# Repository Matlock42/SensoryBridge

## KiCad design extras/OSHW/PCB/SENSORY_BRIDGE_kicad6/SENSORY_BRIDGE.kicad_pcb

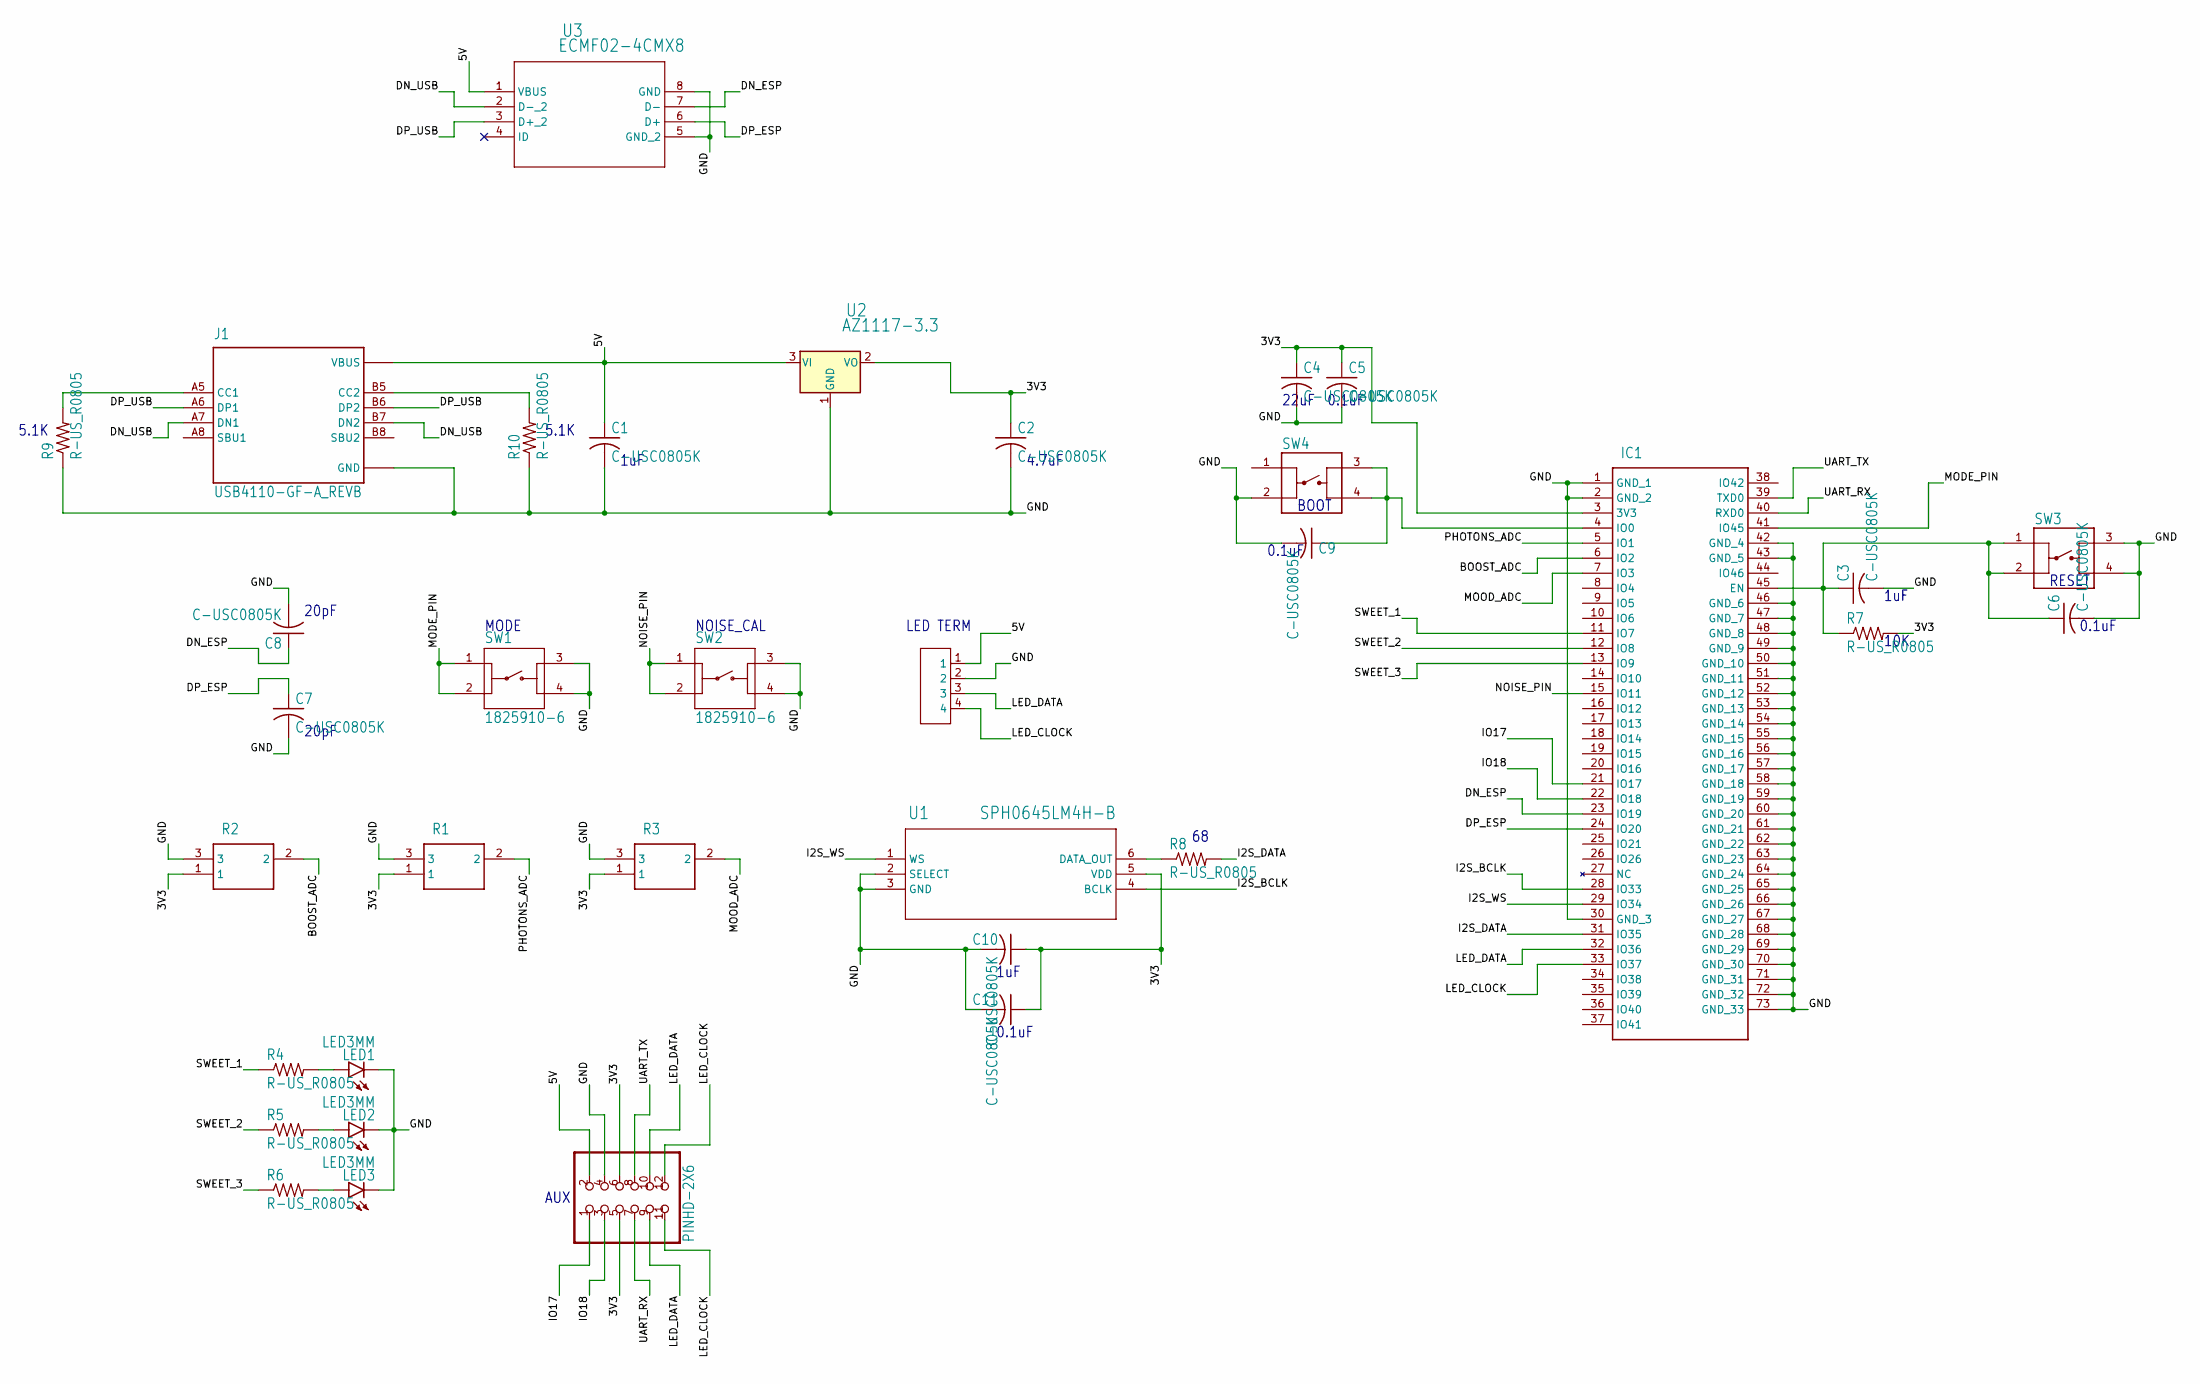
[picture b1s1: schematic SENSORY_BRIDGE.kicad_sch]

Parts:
C1, C2, C3, C4, C5, C6, C7, C8, C9, C10, C11: C-USC0805K; C0805K
IC1: ESP32-S2-MINI-1-N4R2; ESP32S2MINI1N4R2
J1: USB4110-GF-A_REVB; GCT_USB4110-GF-A_REVB
J2: 796949-4; TE_796949-4
JP1: PINHD-2X6; 2X06
LED1, LED2, LED3: LED3MM
R1, R2, R3: 3386P-1-103LF; 3386P_1
R4, R5, R6, R7, R8, R9, R10: R-US_R0805; R0805
SW1, SW2: 1825910-6; SW_1825910-6-4
SW3, SW4: PTS525SM15SMTR2LFS; SW_PTS525SM15SMTR2LFS
U1: SPH0645LM4H-B; SPH0645LM4H-B_KNO
U2: AZ1117-3.3; SOT-223_DIO-M
U3: ECMF02-4CMX8; MICRO_QFN-8L_STM

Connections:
/3V3: C2.1, C4.1, C5.1, C10.1, C11.1, IC1.3 (3V3), JP1.5, JP1.6, R1.1, R2.1, R3.1, R7.2, U1.5 (VDD), U2.2 (VO)
/5V: C1.1, J1.A4/B9 (VBUS), J1.B4/A9 (VBUS), J2.1, JP1.2, U2.3 (VI), U3.1 (VBUS)
/BOOST_ADC: IC1.6 (IO2), R2.2
/DN_ESP: C8.1, IC1.23 (IO19), U3.7 (D-)
/DN_USB: J1.A7 (DN1), J1.B7 (DN2), U3.2 (D-_2)
/DP_ESP: C7.1, IC1.24 (IO20), U3.6 (D+)
/DP_USB: J1.A6 (DP1), J1.B6 (DP2), U3.3 (D+_2)
/GND: C1.2, C2.2, C3.2, C4.2, C5.2, C6.2, C7.2, C8.2, C9.2, C10.2, C11.2, IC1.1 (GND_1), IC1.2 (GND_2), IC1.30 (GND_3), IC1.42 (GND_4), IC1.43 (GND_5), IC1.46 (GND_6), IC1.47 (GND_7), IC1.48 (GND_8), IC1.49 (GND_9), IC1.50 (GND_10), IC1.51 (GND_11), IC1.52 (GND_12), IC1.53 (GND_13), IC1.54 (GND_14), IC1.55 (GND_15), IC1.56 (GND_16), IC1.57 (GND_17), IC1.58 (GND_18), IC1.59 (GND_19), IC1.60 (GND_20), IC1.61 (GND_21), IC1.62 (GND_22), IC1.63 (GND_23), IC1.64 (GND_24), IC1.65 (GND_25), IC1.66 (GND_26), IC1.67 (GND_27), IC1.68 (GND_28), IC1.69 (GND_29), IC1.70 (GND_30), IC1.71 (GND_31), IC1.72 (GND_32), IC1.73 (GND_33), J1.A1/B12 (GND), J1.B1/A12 (GND), J1.S1 (GND), J1.S2 (GND), J1.S3 (GND), J1.S4 (GND), J2.2, JP1.4, LED1.K (C), LED2.K (C), LED3.K (C), R1.3, R2.3, R3.3, R9.1, R10.1, SW1.3, SW1.4, SW2.3, SW2.4, SW3.3, SW3.4, SW4.2, U1.2 (SELECT), U1.3 (GND), U2.1 (GND), U3.5 (GND_2), U3.8 (GND)
/I2S_BCLK: IC1.28 (IO33), U1.4 (BCLK)
/I2S_DATA: IC1.31 (IO35), R8.2
/I2S_WS: IC1.29 (IO34), U1.1 (WS)
/IO17: IC1.21 (IO17), JP1.1
/IO18: IC1.22 (IO18), JP1.3
/LED_CLOCK: IC1.33 (IO37), J2.4, JP1.11, JP1.12
/LED_DATA: IC1.32 (IO36), J2.3, JP1.9, JP1.10
/MODE_PIN: IC1.41 (IO45), SW1.1, SW1.2
/MOOD_ADC: IC1.7 (IO3), R3.2
/NOISE_PIN: IC1.15 (IO11), SW2.1, SW2.2
/PHOTONS_ADC: IC1.5 (IO1), R1.2
/SWEET_1: IC1.11 (IO7), R4.1
/SWEET_2: IC1.12 (IO8), R5.1
/SWEET_3: IC1.13 (IO9), R6.1
/UART_RX: IC1.40 (RXD0), JP1.7
/UART_TX: IC1.39 (TXD0), JP1.8
unnamed: C3.1, C6.1, IC1.45 (EN), R7.1, SW3.1, SW3.2
unnamed: C9.1, IC1.4 (IO0), SW4.3, SW4.4
unnamed: J1.A5 (CC1), R9.2
unnamed: J1.B5 (CC2), R10.2
unnamed: LED1.A, R4.2
unnamed: LED2.A, R5.2
unnamed: LED3.A, R6.2
unnamed: R8.1, U1.6 (DATA_OUT)

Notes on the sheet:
1uF
5.1K
MODE
RESET
BOOT
4.7uF
0.1uF
22uF
AUX
20pF
LED TERM
10K
NOISE_CAL

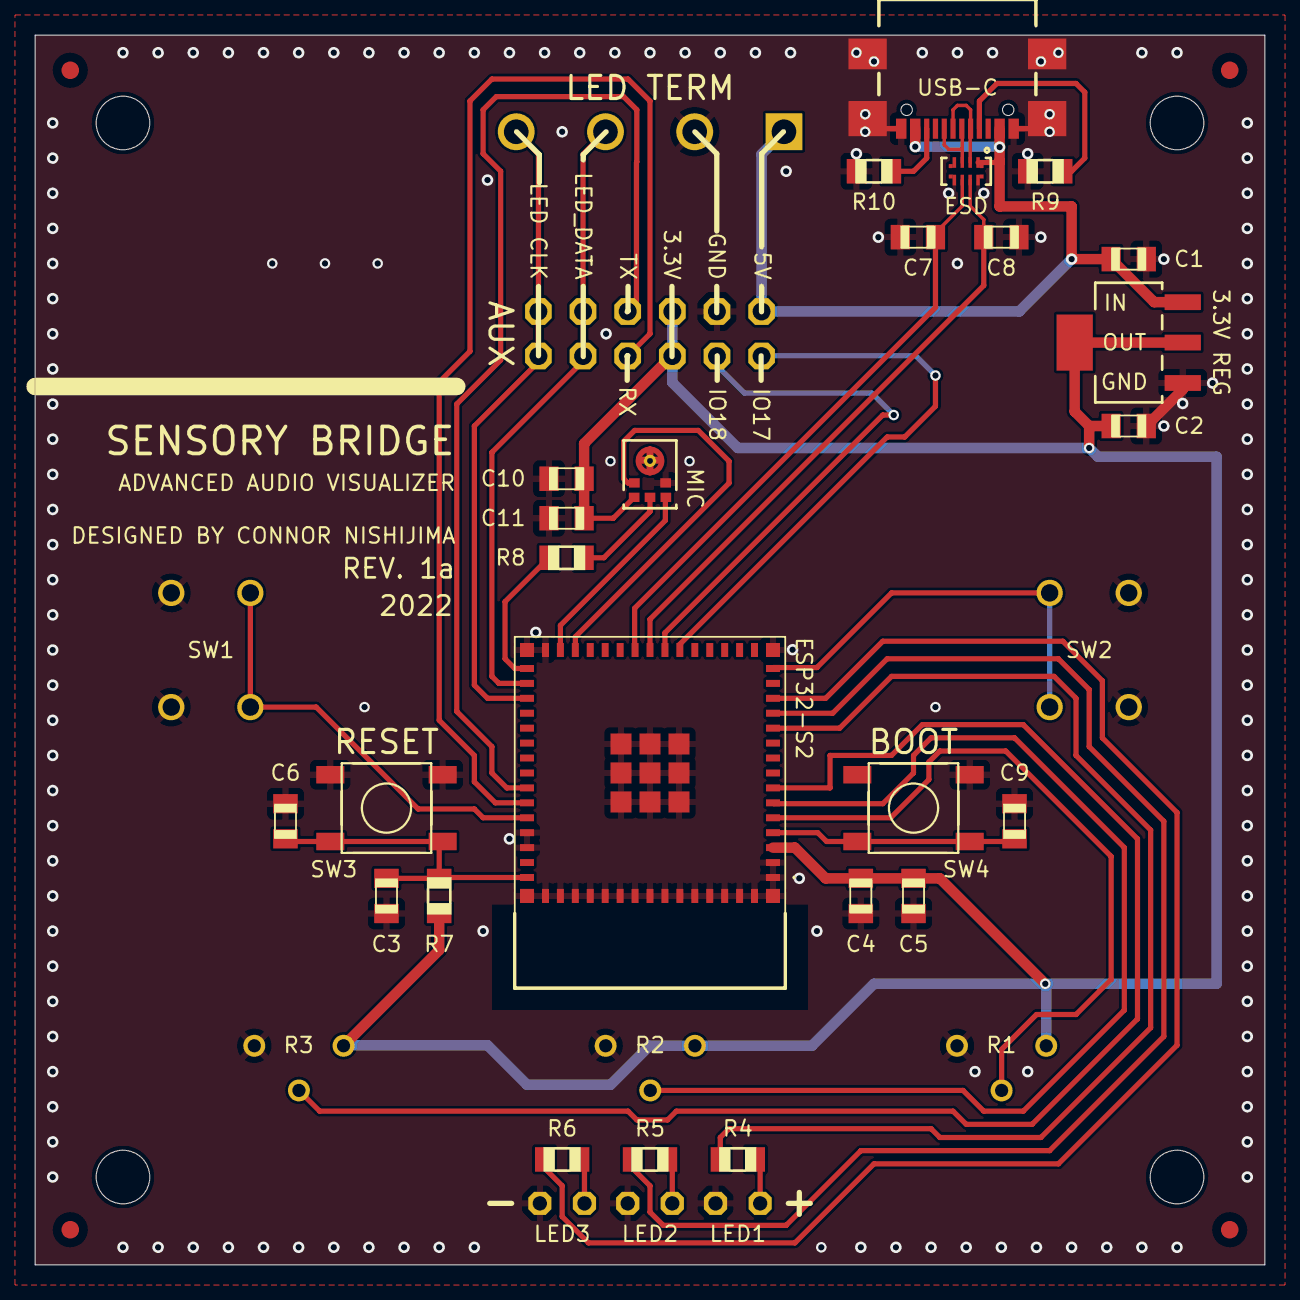
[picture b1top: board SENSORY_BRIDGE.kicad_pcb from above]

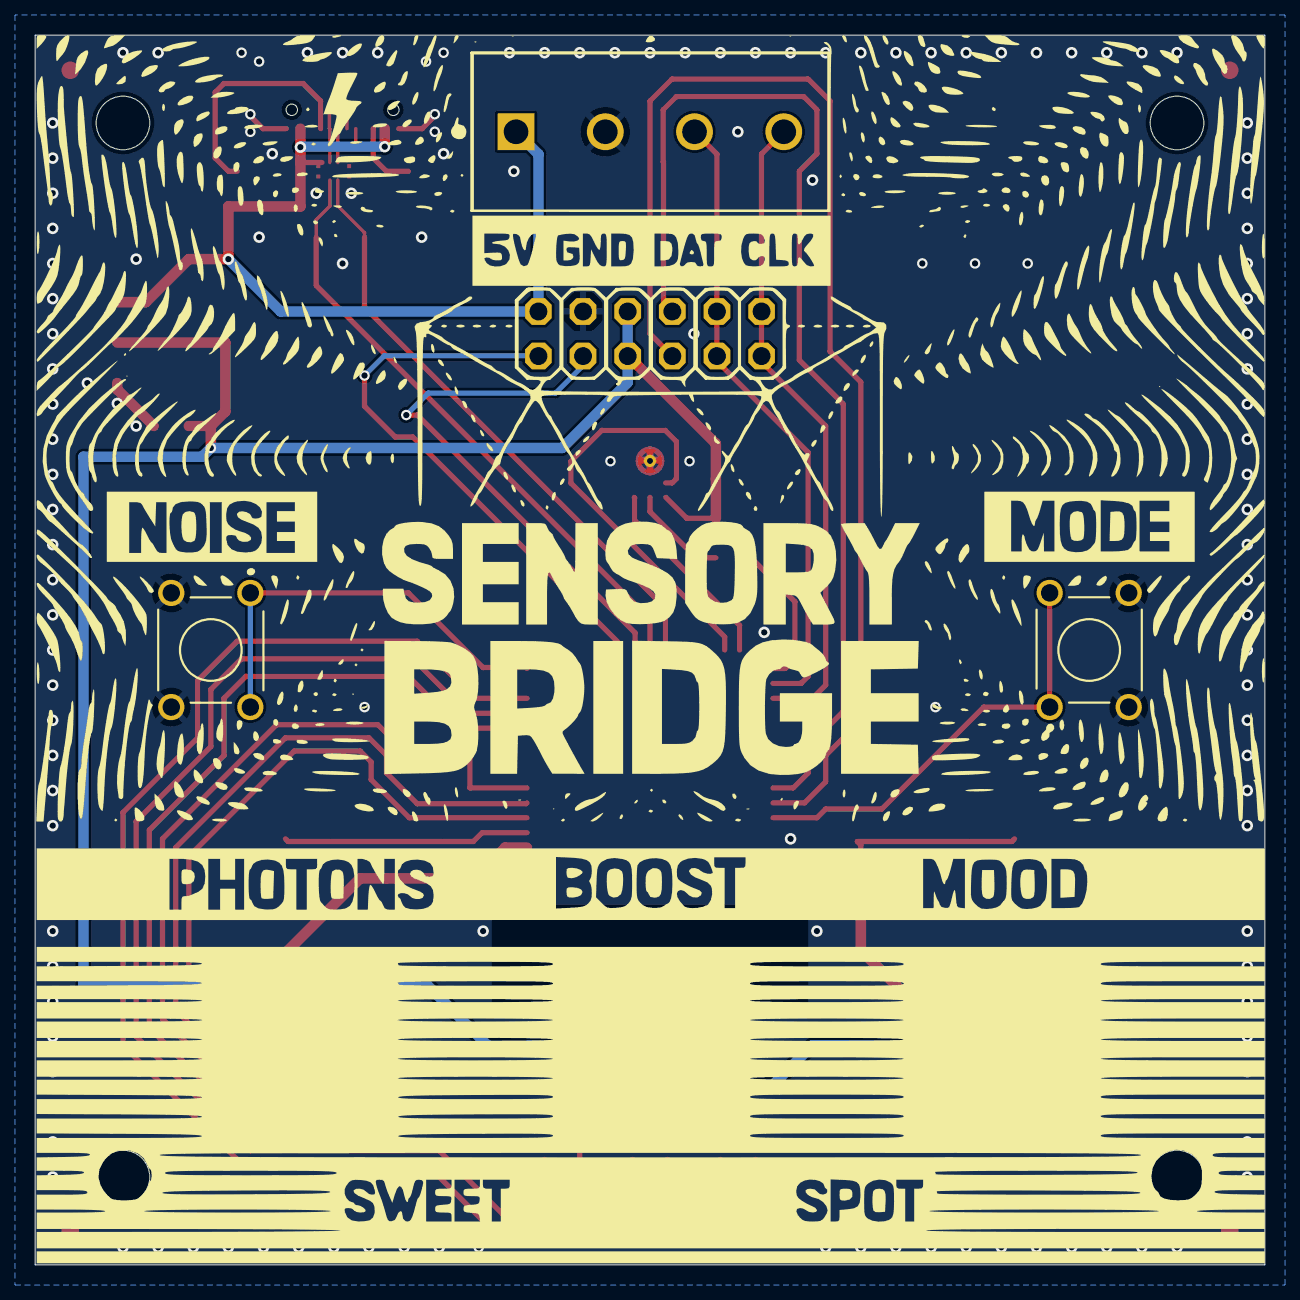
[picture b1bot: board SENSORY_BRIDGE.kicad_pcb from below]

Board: 2 copper layers, 70.0 x 70.0 mm, 43 parts (10 on the bottom side), 32 nets.

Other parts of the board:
@HOLE0, @HOLE1, @HOLE2, @HOLE3: (no value)
U$1, U$2, U$3, U$4: CIRCLE-1MM-2R

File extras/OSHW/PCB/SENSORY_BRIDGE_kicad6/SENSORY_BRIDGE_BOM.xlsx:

Index | Quantity | Part Number | Manufacturer Part Number | Description | Customer Reference | Available | Backorder | Unit Price | Extended Price USD
1 | 1 | 796949-4-ND | 796949-4 | TERM BLK 4P SIDE ENT 5.08MM PCB | J2 | 1 | 0 | 2.93000 | 2.93
2 | 1 | 1965-ESP32-S2-MINI-1-N4R2CT-ND | ESP32-S2-MINI-1-N4R2 | SMD MOD ESP32-S2FN4R2 PCB ANT | IC1 | 1 | 0 | 2.32000 | 2.32
3 | 1 | 497-13420-1-ND | ECMF02-4CMX8 | CMC 2LN SMD ESD | U3 | 1 | 0 | 0.87000 | 0.87
4 | 1 | AP7361-33E-13DICT-ND | AP7361-33E-13 | IC REG LINEAR 3.3V 1A SOT223 | U2 | 0 | 1 | 0.54000 | 0.54
5 | 2 | CKN9104CT-ND | PTS525SM15SMTR2 LFS | SWITCH TACTILE SPST-NO 0.02A 15V | SW3 | 2 | 0 | 0.65000 | 1.30
6 | 1 | 423-1405-1-ND | SPH0645LM4H-B | CRAWFORD MIC DGT I2S BOTTOM PORT | U1 | 1 | 0 | 3.18000 | 3.18
7 | 1 | 2073-USB4110-GF-A-1-ND | USB4110-GF-A | CONN RCP USB2.0 TYP C 24P SMD RA | J1 | 1 | 0 | 1.35000 | 1.35
8 | 3 | 3386P-103TLF-ND | 3386P-1-103TLF | TRIMMER 10K OHM 0.5W PC PIN TOP | R1, R2, R3 | 3 | 0 | 2.50000 | 7.50
9 | 1 | S7109-ND | PPPC062LFBN-RC | CONN HDR 12POS 0.1 GOLD PCB | JP1 | 1 | 0 | 0.82000 | 0.82
10 | 1 | BL-BGX3V1-ND | BL-BGX3V1 | LED GREEN CLEAR 3M T/H | LED2 | 1 | 0 | 0.27000 | 0.27
11 | 2 | 732-5014-ND | 151033YS03000 | LED YELLOW CLEAR 3MM ROUND T/H | LED1, LED3 | 2 | 0 | 0.18000 | 0.36
12 | 1 | RMCF0805JT30R0CT-ND | RMCF0805JT30R0 | RES 30 OHM 5% 1/8W 0805 | R5 | 1 | 0 | 0.10000 | 0.10
13 | 3 | 738-RMCF0805FT66R5CT-ND | RMCF0805FT66R5 | RES 66.5 OHM 1% 1/8W 0805 | R4, R6 | 3 | 0 | 0.10000 | 0.30
14 | 1 | YAG3758CT-ND | AC0805JR-0710KL | RES SMD 10K OHM 5% 1/8W 0805 | R7 | 1 | 0 | 0.10000 | 0.10
15 | 2 | YAG3744CT-ND | AC0805FR-075K1L | RES SMD 5.1K OHM 1% 1/8W 0805 | R9 | 2 | 0 | 0.10000 | 0.20
16 | 4 | 1276-1099-1-ND | CL21B104KACNNNC | CAP CER 0.1UF 25V X7R 0805 | C5 | 4 | 0 | 0.10000 | 0.40
17 | 3 | 1276-1066-1-ND | CL21B105KAFNNNE | CAP CER 1UF 25V X7R 0805 | C1 | 3 | 0 | 0.10000 | 0.30
18 | 2 | 399-C0805C200J5HAC7800CT-ND | C0805C200J5HAC7800 | CAP CER 20PF 50V X8R 0805 | C7 | 2 | 0 | 0.10000 | 0.20
19 | 1 | 1276-6460-1-ND | CL21A226MQQNNNG | CAP CER 22UF 6.3V X5R 0805 | C4 | 1 | 0 | 0.13000 | 0.13
20 | 1 | 1276-1244-1-ND | CL21A475KAQNNNE | CAP CER 4.7UF 25V X5R 0805 | C2 | 1 | 0 | 0.10000 | 0.10
21 | 1 | AZ1117IH-3.3TRG1DICT-ND | AZ1117IH-3.3TRG1 | IC REG LINEAR 3.3V 1A SOT223 | U2 Alt (chng pins) | 1 | 0 | 0.40000 | 0.40
22 | 2 | 2223-TS02-66-60-BK-160-LCR-D-ND | TS02-66-60-BK-160-LCR-D | 6 X 6 MM, 6 MM ACTUATOR HEIGHT, |  | 2 | 0 | 0.10000 | 0.20

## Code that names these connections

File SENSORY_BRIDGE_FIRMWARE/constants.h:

#define SAMPLE_RATE  18750
#define BUFFER_SIZE  256
#define I2S_PORT     I2S_NUM_0

#define FFT_HISTORY_LEN            6
#define AMBIENT_NOISE_SAMPLES      10

#define SWEET_SPOT   0.45F

#define PHOTONS_PIN  1
#define BOOST_PIN    2
#define MOOD_PIN     3

#define SWEET_SPOT_LEFT_PIN    7
#define SWEET_SPOT_CENTER_PIN  13
#define SWEET_SPOT_RIGHT_PIN   9

#define NOISE_CAL_PIN  4
#define MODE_PIN       5

#define NUM_LEDS       10
#define LED_DATA_PIN   8
#define LED_CLOCK_PIN  37

#define I2S_BCLK_PIN   33
#define I2S_LRCLK_PIN  34
#define I2S_DOUT_PIN   24

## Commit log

2022-09-29 Change regulator layout to accept AZ1117IH-3.3TRG1 and similar voltage regulator
    I haven't worked with Eagle so I converted design to KiCad for these changes. The graphics didn't export/import well so I generated the gerber files (1a) and overwrote the back silkscreen with the or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
2022-09-30 Fixed pads for mems microphone and mounting holes
    Also added BOM
2022-10-02 Port SensoryBridge to CircuitPlayground
    Adafruit CircuitPlayground has most of the necessary hardware to replicate the functionality already on board. However, LittleFS doesn't appear to be supported on the Nordic nRF52840. This is not a h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
